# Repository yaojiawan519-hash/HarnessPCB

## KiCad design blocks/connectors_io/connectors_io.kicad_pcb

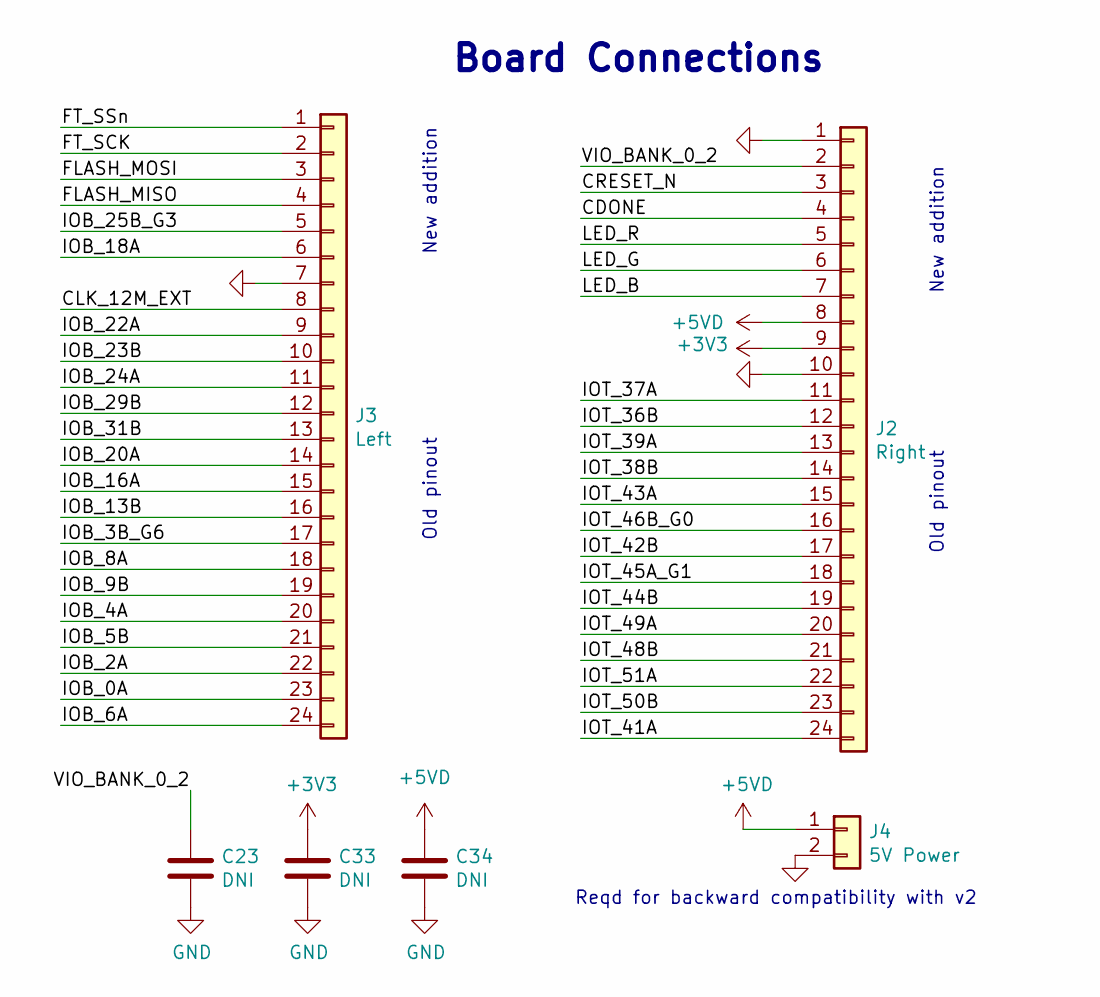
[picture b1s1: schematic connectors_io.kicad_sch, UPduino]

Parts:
C23, C33, C34: DNI; C_0603_1608Metric
J2: Right; PinHeader_1x24_P2.54mm_Vertical
J3: Left; PinHeader_1x24_P2.54mm_Vertical
J4: 5V Power; PinHeader_1x02_P2.54mm_Vertical

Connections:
+3V3: C33.1, J2.9
+5VD: C34.1, J2.8, J4.1
/CDONE: J2.4
/CLK_12M_EXT: J3.8
/CRESET_N: J2.3
/FLASH_MISO: J3.4
/FLASH_MOSI: J3.3
/FT_SCK: J3.2
/FT_SSn: J3.1
/IOB_0A: J3.23
/IOB_2A: J3.22
/IOB_3B_G6: J3.17
/IOB_4A: J3.20
/IOB_5B: J3.21
/IOB_6A: J3.24
/IOB_8A: J3.18
/IOB_9B: J3.19
/IOB_13B: J3.16
/IOB_16A: J3.15
/IOB_18A: J3.6
/IOB_20A: J3.14
/IOB_22A: J3.9
/IOB_23B: J3.10
/IOB_24A: J3.11
/IOB_25B_G3: J3.5
/IOB_29B: J3.12
/IOB_31B: J3.13
/IOT_36B: J2.12
/IOT_37A: J2.11
/IOT_38B: J2.14
/IOT_39A: J2.13
/IOT_41A: J2.24
/IOT_42B: J2.17
/IOT_43A: J2.15
/IOT_44B: J2.19
/IOT_45A_G1: J2.18
/IOT_46B_G0: J2.16
/IOT_48B: J2.21
/IOT_49A: J2.20
/IOT_50B: J2.23
/IOT_51A: J2.22
/LED_B: J2.7
/LED_G: J2.6
/LED_R: J2.5
/VIO_BANK_0_2: C23.1, J2.2
GND: C23.2, C33.2, C34.2, J2.1, J2.10, J3.7, J4.2

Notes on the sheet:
New addition
Board Connections
Reqd for backward compatibility with v2
Old pinout

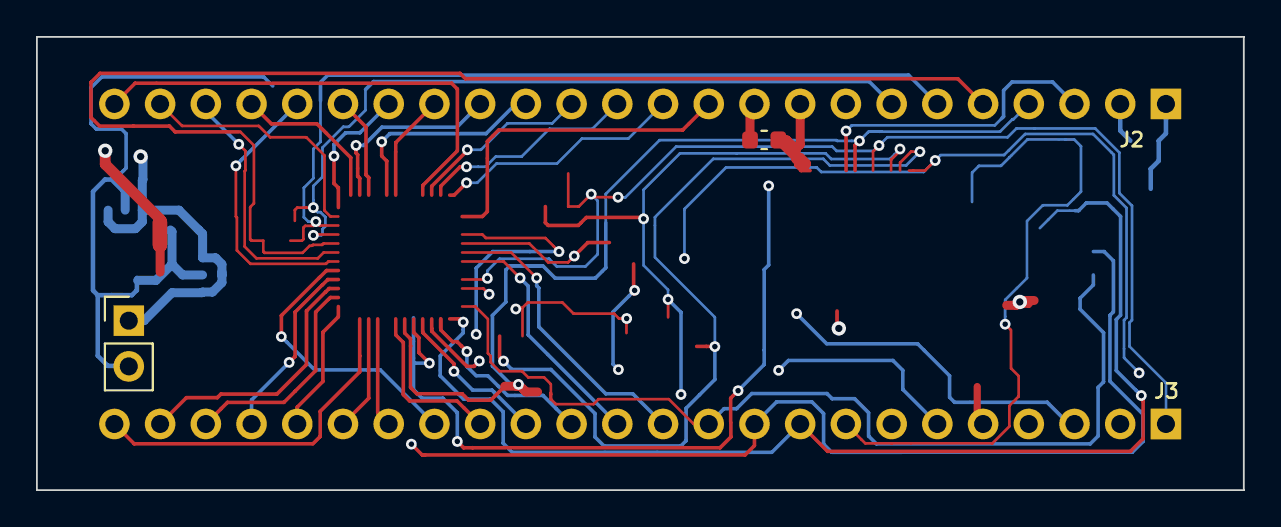
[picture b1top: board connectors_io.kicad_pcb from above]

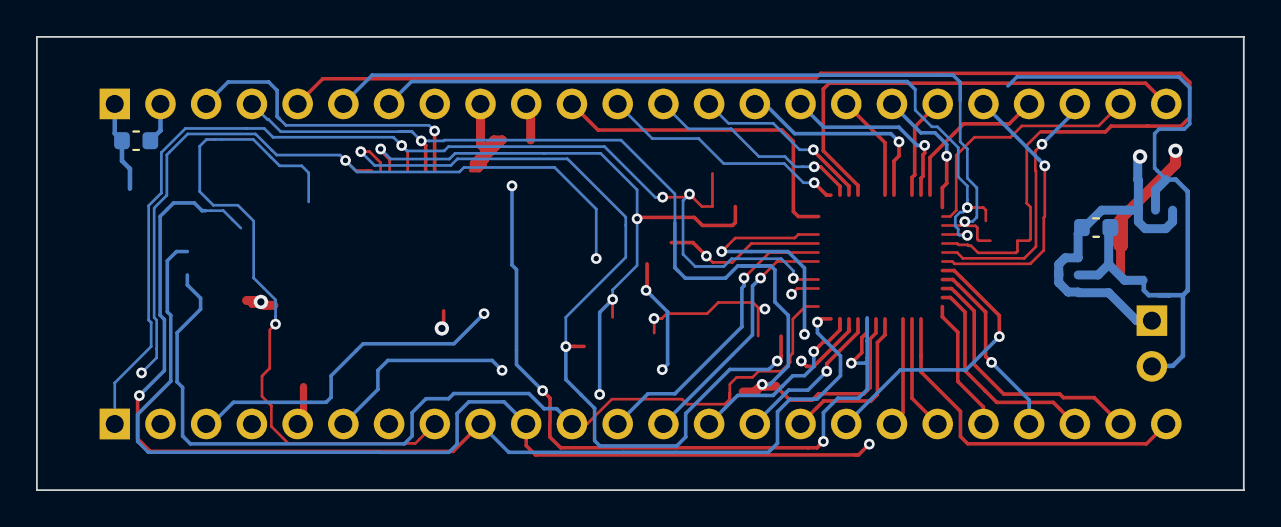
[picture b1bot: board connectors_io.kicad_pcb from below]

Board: 4 copper layers, 67.0 x 25.2 mm, 6 parts (2 on the bottom side), 4 nets.

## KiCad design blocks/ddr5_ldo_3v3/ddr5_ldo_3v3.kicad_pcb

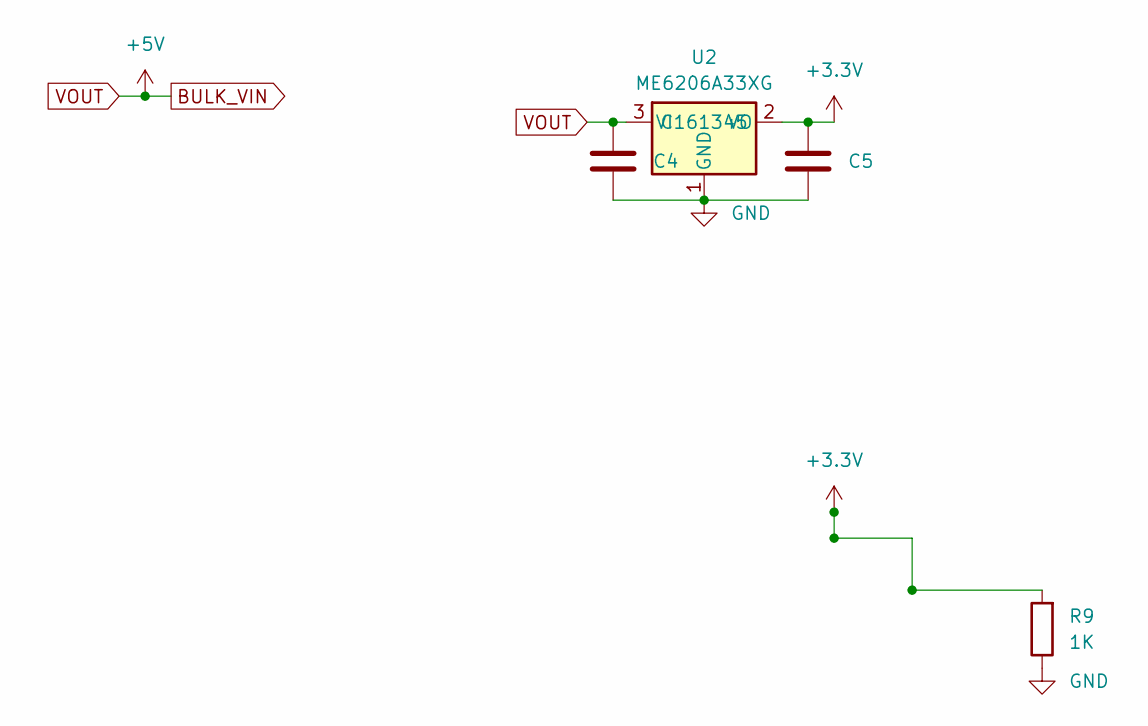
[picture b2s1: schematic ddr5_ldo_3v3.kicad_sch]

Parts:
C4, C5: 10uF/6.3V; C_0805_2012Metric
R9: 1K; R_0805_2012Metric
U2: ME6206A33XG; SOT-23

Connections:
+3.3V: C5.1, R9.2, U2.2 (VO)
BULK_VIN: C4.1, U2.3 (VI)
GND: C4.2, C5.2, R9.1, U2.1 (GND)

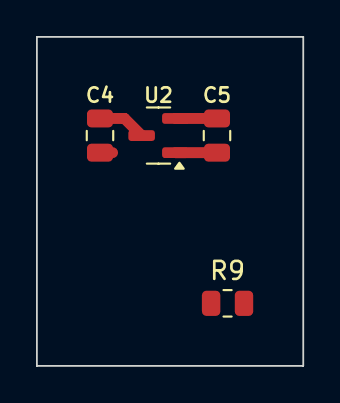
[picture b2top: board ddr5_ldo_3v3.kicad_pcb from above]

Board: 2 copper layers, 14.8 x 18.3 mm, 4 parts (0 on the bottom side), 3 nets.

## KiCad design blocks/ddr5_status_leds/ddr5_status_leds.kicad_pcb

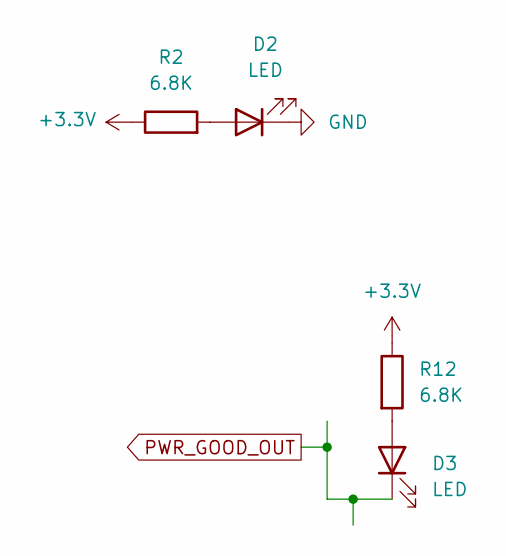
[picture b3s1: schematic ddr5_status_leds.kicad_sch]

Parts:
D2, D3: LED; LED_0805_2012Metric
R2, R12: 6.8K; R_0805_2012Metric

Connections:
+3.3V: R2.1, R12.1
GND: D2.1 (K)
unnamed: D2.2 (A), R2.2
unnamed: D3.2 (A), R12.2
PWR_GOOD_OUT: D3.1 (K)

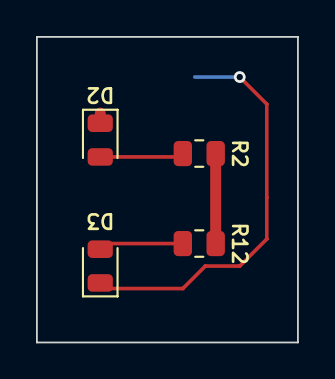
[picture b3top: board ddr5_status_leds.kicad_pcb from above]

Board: 2 copper layers, 14.5 x 17.0 mm, 4 parts (0 on the bottom side), 3 nets.

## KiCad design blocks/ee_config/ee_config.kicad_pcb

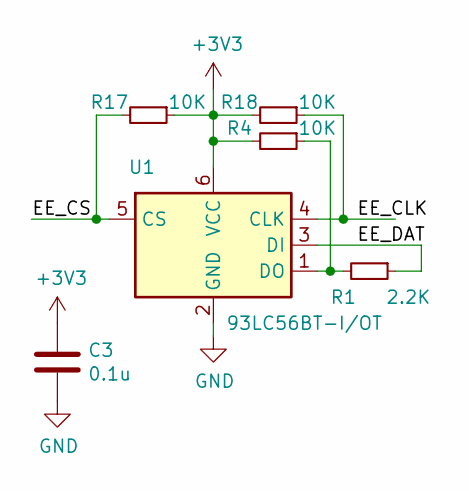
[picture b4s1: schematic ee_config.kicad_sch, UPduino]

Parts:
C3: 0.1u; C_0603_1608Metric
R1: 2.2K; R_0603_1608Metric
R4, R17, R18: 10K; R_0603_1608Metric
U1: 93LC56BT-I/OT; SOT-23-6

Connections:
+3V3: C3.1, R4.2, R17.1, R18.2, U1.6 (VCC)
/EE_CLK: R18.1, U1.4 (CLK)
/EE_CS: R17.2, U1.5 (CS)
/EE_DAT: R1.1, U1.3 (DI)
GND: C3.2, U1.2 (GND)
unnamed: R1.2, R4.1, U1.1 (DO)

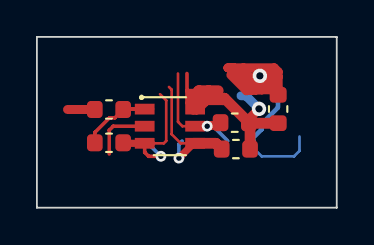
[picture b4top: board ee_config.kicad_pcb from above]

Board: 4 copper layers, 16.7 x 9.5 mm, 6 parts (0 on the bottom side), 6 nets.

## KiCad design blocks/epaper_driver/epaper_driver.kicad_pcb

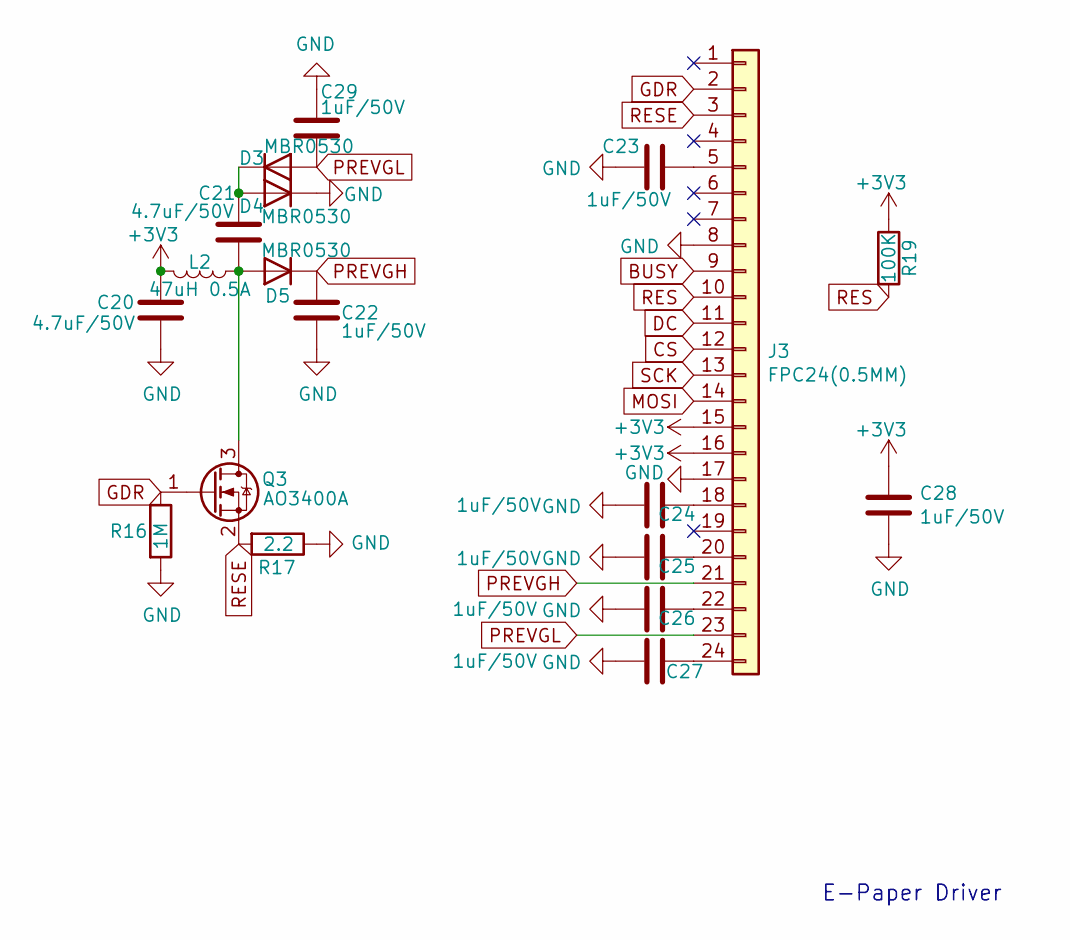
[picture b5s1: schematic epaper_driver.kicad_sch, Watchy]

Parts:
C20, C21: 4.7uF/50V; C_0603_1608Metric
C22, C23, C24, C25, C26, C27, C28, C29: 1uF/50V; C_0402_1005Metric
D3, D4, D5: MBR0530; D_SOD-123
J3: FPC24(0.5MM); 24_Pins_0.5mm_Pitch_ZIF_Connector_UP
L2: 47uH 0.5A; L_Taiyo-Yuden_NR-40xx
Q3: AO3400A; SOT-23
R16: 1M; R_0402_1005Metric
R17: 2.2; R_0402_1005Metric
R19: 100K; R_0402_1005Metric

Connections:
+3V3: C20.1, C28.1, J3.15, J3.16, L2.2, R19.1
BUSY: J3.9
CS: J3.12
DC: J3.11
GDR: J3.2, Q3.1 (G), R16.1
GND: C20.2, C22.2, C23.2, C24.2, C25.2, C26.2, C27.2, C28.2, C29.1, D4.1 (K), J3.8, J3.17, R16.2, R17.1
MOSI: J3.14
unnamed: C21.1, D3.1 (K), D4.2 (A)
unnamed: C21.2, D5.2 (A), L2.1, Q3.3 (D)
unnamed: C23.1, J3.5
unnamed: C24.1, J3.18
unnamed: C25.1, J3.20
unnamed: C26.1, J3.22
unnamed: C27.1, J3.24
PREVGH: C22.1, D5.1 (K), J3.21
PREVGL: C29.2, D3.2 (A), J3.23
RES: J3.10, R19.2
RESE: J3.3, Q3.2 (S), R17.2
SCK: J3.13

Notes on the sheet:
E-Paper Driver

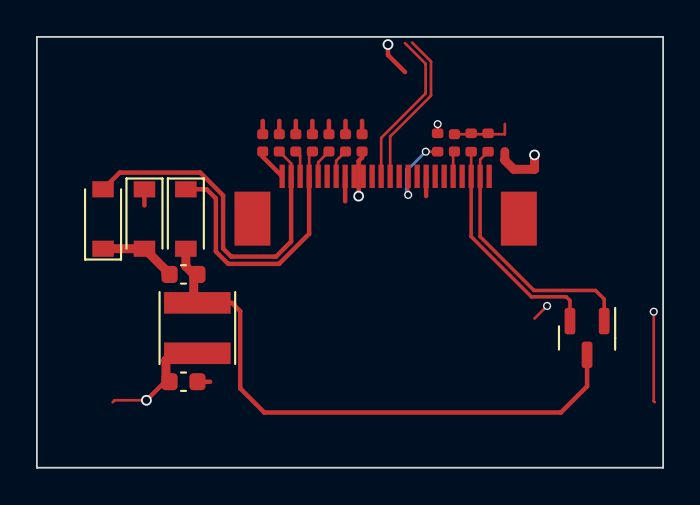
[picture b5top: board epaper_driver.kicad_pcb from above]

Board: 4 copper layers, 34.8 x 23.9 mm, 19 parts (0 on the bottom side), 14 nets.
